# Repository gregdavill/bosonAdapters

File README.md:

# bosonAdapters
Collection of PCB adapters for the bosonFrameGrabber

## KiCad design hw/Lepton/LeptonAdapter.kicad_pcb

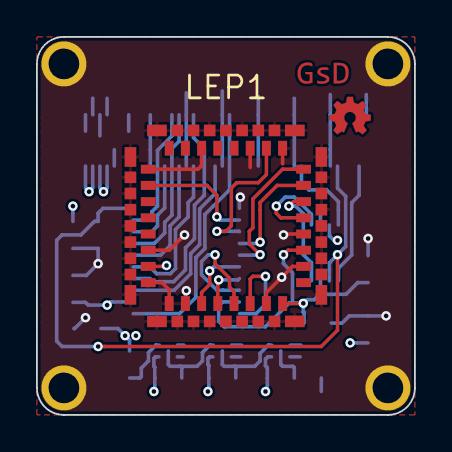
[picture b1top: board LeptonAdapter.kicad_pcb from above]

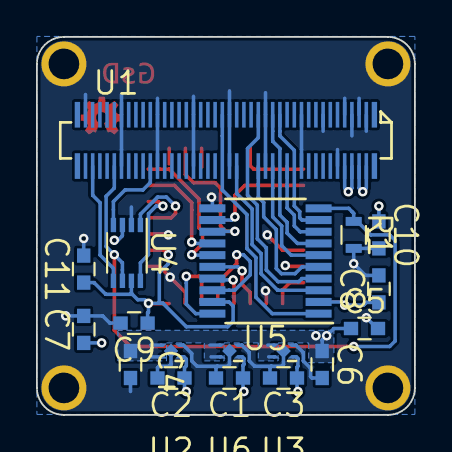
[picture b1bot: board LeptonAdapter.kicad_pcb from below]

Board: 4 copper layers, 21.0 x 21.0 mm, 19 parts (18 on the bottom side), 26 nets.

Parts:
C1, C2, C3, C4, C5: 1uF; C_0603
C6, C7, C8, C9, C10, C11: 100n; C_0603
LEP1: LEPTON; 1050281001
R1: 10k; R_0603
U1: Boson_Slave; DF40_80Pin
U2, U3, U6: TLV733P; X2SON
U4: TXS0102; VSSOP-8_2.3x2mm_Pitch0.5mm
U5: TB0108; TSSOP-20_4.4x6.5mm_Pitch0.65mm

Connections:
+1V2: C2.1, C10.1, LEP1.7, U2.1
+1V8: C1.1, C7.1, C8.1, U4.3, U5.2, U6.1
+2V8: C3.1, C9.1, C11.1, LEP1.16, LEP1.19, U3.1, U4.7, U5.19
+3V3: C4.1, C5.1, C6.1, U1.2, U1.4, U1.6, U1.8, U2.3, U2.4, U3.3, U3.4, U6.3, U6.4
/IIC_SCL: U1.62, U4.4
/IIC_SDA: U1.78, U4.5
/LEP_CLK: LEP1.13, U5.18
/LEP_CS: LEP1.14, U5.20
/LEP_MCLK: LEP1.26, U5.13
/LEP_MISO: LEP1.12, U5.17
/LEP_MOSI: LEP1.11, U5.16
/LEP_PWRDWN: LEP1.23, U5.14
/LEP_RST: LEP1.24, U5.15
/LEP_SCL: LEP1.21, U4.1
/LEP_SDA: LEP1.22, U4.8
/LEP_VSYNC: LEP1.2, U5.12
/MCLK: U1.24, U5.8
/OE: R1.1, U1.72, U4.6, U5.10
/POWER_DOWN: U1.27, U5.7
/RESET: U1.28, U5.6
/SPI_CLK: U1.38, U5.3
/SPI_CS: U1.41, U5.1
/SPI_MISO: U1.31, U5.4
/SPI_MOSI: U1.32, U5.5
/VSYNC: U1.25, U5.9
GND: C1.2, C2.2, C3.2, C4.2, C5.2, C6.2, C7.2, C8.2, C9.2, C10.2, C11.2, LEP1.1, LEP1.6, LEP1.8, LEP1.9, LEP1.10, LEP1.15, LEP1.18, LEP1.20, LEP1.25, LEP1.27, LEP1.30, LEP1.33, R1.2, U1.1, U1.3, U1.5, U1.7, U1.10, U1.13, U1.19, U1.20, U1.29, U1.30, U1.39, U1.40, U1.49, U1.50, U1.59, U1.60, U1.69, U1.70, U1.79, U2.2, U3.2, U4.2, U5.11, U6.2

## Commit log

2018-10-09 Initial Commit of Lepton Adapter
